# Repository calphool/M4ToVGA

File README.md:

# M4ToVGA

M4ToVGA is an FPGA hardware project that allows you to connect your TRS-80 Model 4 or TRS-80 Model 3 to a VGA monitor.  

Although everyone loves the warm glow of a 1980s CRT, these devices are slowly dying (or in my case I received a vintage TRS-80 Model 4 in the mail with a crushed CRT and needed an alternative.)

This project is built around the Cyclone IV FPGA, and more specifically the Core EP4CE6 board that is super cheap (around $20) and contains more than enough logic fabric to do the job.

## Theory of Operation

Although you can find composite boards that will convert the video signals from a TRS-80 Model 3/4 to a composite video signal that can be used with an NTSC television, most of these are based on the video output circuitry of the TRS-80 Model 1, which contains a video mixing circuit capable of mixing vsync, hsync, and video out into a *roughly* conforming NTSC composite signal.  Unfortunately, the timing of the Model 3/4 video output is a little bit different than the Model 1, and thus many people struggle to use these composite boards successfully unless their television has a means of shifting and stretching the video signal.

Although I was able to get one of these circuits to work *more or less*, I was unsatisfied with the results, and I wanted to learn how to code Verilog for FPGAs anyway, so I thought this would be a good time to learn.

The code has five main blocks (or modules).  

* It has a "top" module whose job is to stitch all the submodules together into a meaningful circuit.  
* The submodules include a PLL based clock for the VGA signal (25MHZ for 640x480 resolution).  
* The next submodule is a framebuffer that is 153,600 x 1 bits, which works to store a 640 x 240 array of pixels, the maximum resolution of a TRS-80 Model 3/4.  Those two submodules were generated in Quartus II using wizards.  
* Next is a VGA output module whose job is to take in the VGA clock and continuously scan through the framebuffer and display what it sees there.  It has a sub-sub-module whose job is to produce vga hsync and vsync as well as inform the VGA output module when the signal is "in the display zone," as opposed to one of the vertical or horizontal blank areas.
* Finally is the m4_input module, whose job is to monitor the Model 3/Model 4 hsync, vsync, dot clock, and video signals, interpret them, and turn them into bits (pixels) in the dual port frame buffer.
 The dotclk signal was actually removed in the M3 code because we don't need it. The M3 only has one resolution and we can synthesize the dotclk and keep it in aligned using 
hsync.  It is *probably* possible to remove it for the M4 as well, but I would have to contend with the fact that the dot clock changes due to the M4's ability to switch between 64 and 80 column mode.

## Details

Below you will see oscilloscope pictures showing the hsync, vsync, and video traces from a TRS-80 Model 4 (ignore the "Model 3" text, it's a typo).  

These signals are all driven and synchronized by an underlying "dot clock."

These signals are what we needed to transform into a VGA signal, and what the m4_input submodule contends with.

Below you see a graphic of the top module that ties together all the submodules.

## Status

**2021, April 18**

A few updates.  First, I bought a Nandland Go board because I like how the designer (Russell) has put together a lot of training material.  I am thinking of going through 
his training projects to pick up tips / tricks.  No intent to convert the MXToVGA projects away from Altera, but I sure would like to get a more solid understanding of 
how hardware engineers like Russell build rock solid projects.  Oh, I also updated all the code in this repo to use Russell's naming standard.  He's right, it makes the 
code easier to understand.

As you may have figured out, I have bifurcated (trifurcated?) the project into three separate repositories (M4ToVGA, M2ToVGA, and M3ToVGA).  M4ToVGA and M3ToVGA are known to be working.
M2ToVGA is *close* to working, but seems to still exhibit some jitter.  I am waiting to borrow an M2 from someone in order to work out what exactly is going on.  Since the 
fix for the M3ToVGA from the M4ToVGA base code was to add another flip flop in the video input chain, I have little doubt that there is something similar going on somewhere,
in the M2ToVGA code, but the trick is finding it, and that takes a degree of trial and error.  Once I get three separate repos that work (and thus can ship a working board for all three 
systems), I will probably spend some time figuring out how I can merge the code bases.  They're *very* similar, so it seems reasonable that they could be merged, which 
would be easier to maintain.  

I also just bought some LM1881 sync splitter chips, and so I'll be embarking on an effort to figure out if it's possible to build a 
VGA adapter for the Model 1 that does not require modifying the system.  In theory, if I can get the signals split out, then the exercise becomes similar to the MXToVGA 
projects.  It would be nice to build it so that it doesn't need an external power source, and I think there's a +5V signal available in the video DIN, but I'm not sure 
how much current can be drawn from it.  More details later.

**2021, February 20**

Updated the M4ToVGA code to get rid of the top and bottom line.  Now it has a temporary logo that disappears after 10 seconds.

**2021, January 20**

I have begun shipping the first few copies of the 1.1 VGA board, which includes some location fixes for components.  There is one remaining "slighly off"
location for the power pins for the FPGA, but it is close enough that if I solder the pins after the two boards are mated it still works okay.  I 
will fix it in the 1.2 version of the board if I get through the 20+ 1.1 boards I have.  I may also do something different with the location of the 
power regulators.  They are oriented vertically toward the bottom of the board, which is a little non-aesthetic since they stand up like tombstones.

I want to get the board out to a few people before opening the flood gates.  I'm well aware that it has only been tested on my M4, and so as people 
begin trying it on M2s and M3s, I want to see what the results are.  It *appears* that it should work just fine, and may even work on an M1 with the 
right signal placement, but I'm well aware that with hardware you never know for sure until you've actually seen the results.

I did some experimentation with providing my own on-board clock and ignoring the dot clock from the TRS-80, which produced something that *kind of* works. I 
would need to oversample the signals considerably (probably at least 10X) and then come up with an algorithm for using the oversampled 
signals, and at this point that's just a bit beyond my Verilog skills.  I'll probably keep toying around with it over time.  It's clearly possible, but 
just not as easy as taking the dot clock from the motherboard and using it to synchronize the incoming video.  I suspect this is why many -ToVGA boards 
have subtle issues that require options and menu systems to work around.  For now the production version of the board still requires the dot clock.

**2020, December 15**

I did eventually figure out how to clear the BRAM when the mode switches from 80 to 64 column mode.  It took way more work than I expected.  The solution was 
relatively simple, but getting there was not.

Got the PCB, populated it.  Worked as intended.  I'm working on another revision though because I don't care for a few of the placement decisions I made.
I also need to add a pin header so that the board can be used on something other than the Model 3/4 AMP connector.  I also realized that soldering 0603 LEDs 
is a pain in the neck, so I switched all those out to small through-hole LEDs.

I don't care for the DOT CLK situation.  I'd like to get rid of the dot clock, but I haven't come up with a solution yet.

I've also been digging into DVI/HDMI via FPGA.  There is apparently an open source HDMI implementation now, so the question is will it work for a Cyclone IV
board?  It looks like it might.  How cool would it be to have simultaneous VGA and HDMI out?  Might be a pipe dream, but it's something I'll keep digging into.
We'll see...

**2020, November 26**

Happy Thanksgiving for those in the USA!  It's not exactly a pleasant one for most folks as the "human-malware" continues to spread and 
most folks are limiting their get-togethers in one form or another.

Well, I made some tweaks to the code to deal with the fact that 80-column mode on the TRS-80 Model 4 has a different dot clock than 
64 column mode.  Without these changes the right side of 80 column mode was chopped off.  At vertical blank, the code resets the 
counter it uses to count how many dots there were per horizontal line, which allows the code to switch back and forth between modes.

There's one remaining issue, which is that since 80 column mode uses the entire screen worth of pixels, when you switch back to 
64 column mode there is sometimes garbage left on the right and left sides of the screen.  I'll have to work some kind of "one frame of 
clearing the dual port ram" when a change is detected into the design.

I also think I'd like to have some way to change the amount that the screen shifts left/right and maybe top/bottom.  Ideally it would 
be a potentiometer or rotational encoder, though I'm not sure how you interface either of them to an FPGA and I'd rather not have to 
introduce an ADC to the design if I can help it.  Ideally two additional pots/encoders would let you shrink or expand the screen as well,
but that will probably have to wait a bit.  In any event, I'll be digging into how to potentiometers/encoders these into the design shortly.

**2020, November 23**

The current version works, but isn't complete.  I'll need to design a PCB next and finish its testing to produce a version 1.0.

## License
[MIT](https://choosealicense.com/licenses/mit/)

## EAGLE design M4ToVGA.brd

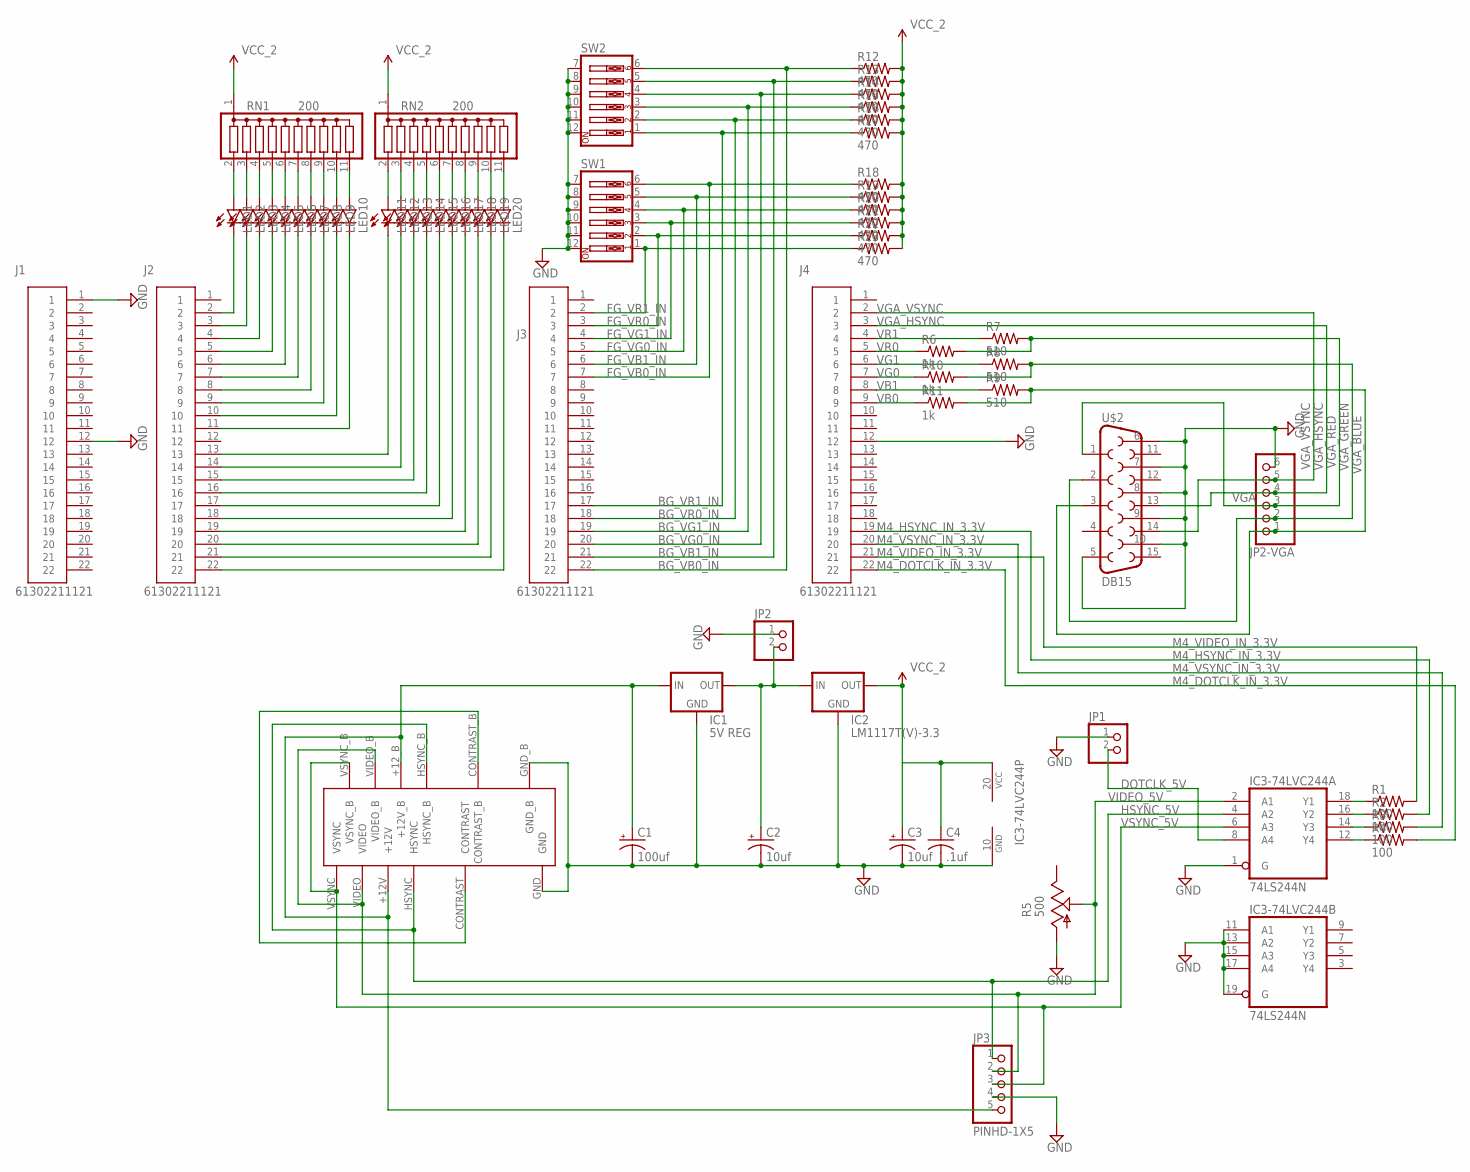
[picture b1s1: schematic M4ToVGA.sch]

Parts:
C1: 100uf; E2,5-5
C2, C3: 10uf; E2,5-5
C4: .1uf; C025-025X050
IC1: 5V REG; 78XXS
IC2: LM1117T(V)-3.3; TO220V
IC3-74LVC244: 74LS244N; DIL20
J1, J2, J3, J4: 61302211121
JP1, JP2: PINHD-1X2; 1X02
JP2-VGA: VGA; 1X06
JP3: PINHD-1X5; 1X05
LED1, LED2, LED3, LED4, LED5, LED6, LED7, LED8, LED9, LED10, LED11, LED12, LED13, LED14, LED15, LED16, LED17, LED18, LED19, LED20: LED3MM
R1, R2, R3, R4: 100; 0204/7
R5: 500; B25P
R6, R10, R11: 1k; 0204/7
R7, R8, R9: 510; 0204/7
R12, R13, R14, R15, R16, R17, R18, R19, R20, R21, R22, R23: 470; 0204/7
RN1, RN2: 200; SIL11
SW1, SW2: SW_DIP-6; EDG-06
U$1: AMP-583479-1-CARD-EDGE; AMP583479-1
U$2: DB15

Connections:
+5V: C2.+, IC1.OUT, IC2.3 (IN), JP2.2
+12V: C1.+, IC1.IN, JP3.5, U$1.+12V, U$1.+12_B (+12V_B)
BG_VB0_IN: J3.22, R12.1, SW2.6
BG_VB1_IN: J3.21, R13.1, SW2.5
BG_VG0_IN: J3.20, R14.1, SW2.4
BG_VG1_IN: J3.19, R15.1, SW2.3
BG_VR0_IN: J3.18, R16.1, SW2.2
BG_VR1_IN: J3.17, R17.1, SW2.1
DOTCLK_5V: IC3-74LVC244.8 (A4), JP1.2
FG_VB0_IN: J3.7, R18.1, SW1.6
FG_VB1_IN: J3.6, R19.1, SW1.5
FG_VG0_IN: J3.5, R20.1, SW1.4
FG_VG1_IN: J3.4, R21.1, SW1.3
FG_VR0_IN: J3.3, R22.1, SW1.2
FG_VR1_IN: J3.2, R23.1, SW1.1
GND: C1.-, C2.-, C3.-, C4.2, IC1.GND, IC2.1 (GND), IC3-74LVC244.1 (G), IC3-74LVC244.10 (GND), IC3-74LVC244.11 (A1), IC3-74LVC244.13 (A2), IC3-74LVC244.15 (A3), IC3-74LVC244.17 (A4), IC3-74LVC244.19 (G), J1.1, J1.12, J4.12, JP1.1, JP2.1, JP2-VGA.6, JP3.4, R5.A, SW1.7, SW1.8, SW1.9, SW1.10, SW1.11, SW1.12, SW2.7, SW2.8, SW2.9, SW2.10, SW2.11, SW2.12, U$1.GND, U$1.GND_B, U$2.5, U$2.6, U$2.7, U$2.8, U$2.9, U$2.10
HSYNC_5V: IC3-74LVC244.4 (A2), JP3.1, U$1.HSYNC, U$1.HSYNC_B
M4_DOTCLK_IN_3.3V: J4.22, R4.2
M4_HSYNC_IN_3.3V: J4.19, R2.2
M4_VIDEO_IN_3.3V: J4.21, R1.2
M4_VSYNC_IN_3.3V: J4.20, R3.2
unnamed: IC3-74LVC244.18 (Y1), R1.1
unnamed: IC3-74LVC244.16 (Y2), R2.1
unnamed: IC3-74LVC244.14 (Y3), R3.1
unnamed: IC3-74LVC244.12 (Y4), R4.1
unnamed: LED1.A, RN1.2
unnamed: U$1.CONTRAST, U$1.CONTRAST_B
unnamed: LED2.A, RN1.3
unnamed: LED3.A, RN1.4
unnamed: LED4.A, RN1.5
unnamed: LED5.A, RN1.6
unnamed: LED6.A, RN1.7
unnamed: LED7.A, RN1.8
unnamed: LED8.A, RN1.9
unnamed: LED9.A, RN1.10
unnamed: LED10.A, RN1.11
unnamed: LED11.A, RN2.2
unnamed: LED12.A, RN2.3
unnamed: LED13.A, RN2.4
unnamed: LED14.A, RN2.5
unnamed: LED15.A, RN2.6
unnamed: LED16.A, RN2.7
unnamed: LED17.A, RN2.8
unnamed: LED18.A, RN2.9
unnamed: LED19.A, RN2.10
unnamed: LED20.A, RN2.11
OUTPUTLEDA_0: J2.11, LED10.K (C)
OUTPUTLEDA_1: J2.10, LED9.K (C)
OUTPUTLEDA_2: J2.9, LED8.K (C)
OUTPUTLEDA_3: J2.8, LED7.K (C)
OUTPUTLEDA_4: J2.7, LED6.K (C)
OUTPUTLEDA_5: J2.6, LED5.K (C)
OUTPUTLEDA_6: J2.5, LED4.K (C)
OUTPUTLEDA_7: J2.4, LED3.K (C)
OUTPUTLEDA_8: J2.3, LED2.K (C)
OUTPUTLEDA_9: J2.2, LED1.K (C)
OUTPUTLEDB_0: J2.22, LED20.K (C)
OUTPUTLEDB_1: J2.21, LED19.K (C)
OUTPUTLEDB_2: J2.20, LED18.K (C)
OUTPUTLEDB_3: J2.19, LED17.K (C)
OUTPUTLEDB_4: J2.18, LED16.K (C)
OUTPUTLEDB_5: J2.17, LED15.K (C)
OUTPUTLEDB_6: J2.16, LED14.K (C)
OUTPUTLEDB_7: J2.15, LED13.K (C)
OUTPUTLEDB_8: J2.14, LED12.K (C)
OUTPUTLEDB_9: J2.13, LED11.K (C)
VB0: J4.9, R11.1
VB1: J4.8, R9.1
VCC_2: C3.+, C4.1, IC2.2 (OUT), IC3-74LVC244.20 (VCC), R12.2, R13.2, R14.2, R15.2, R16.2, R17.2, R18.2, R19.2, R20.2, R21.2, R22.2, R23.2, RN1.1, RN2.1
VG0: J4.7, R10.1
VG1: J4.6, R8.1
VGA_BLUE: JP2-VGA.1, R9.2, R11.2, U$2.3
VGA_GREEN: JP2-VGA.2, R8.2, R10.2, U$2.2
VGA_HSYNC: J4.3, JP2-VGA.4, U$2.13
VGA_RED: JP2-VGA.3, R6.2, R7.2, U$2.1
VGA_VSYNC: J4.2, JP2-VGA.5, U$2.14
VIDEO_5V: IC3-74LVC244.2 (A1), JP3.2, R5.S, U$1.VIDEO, U$1.VIDEO_B
VR0: J4.5, R6.1
VR1: J4.4, R7.1
VSYNC_5V: IC3-74LVC244.6 (A3), JP3.3, U$1.VSYNC, U$1.VSYNC_B

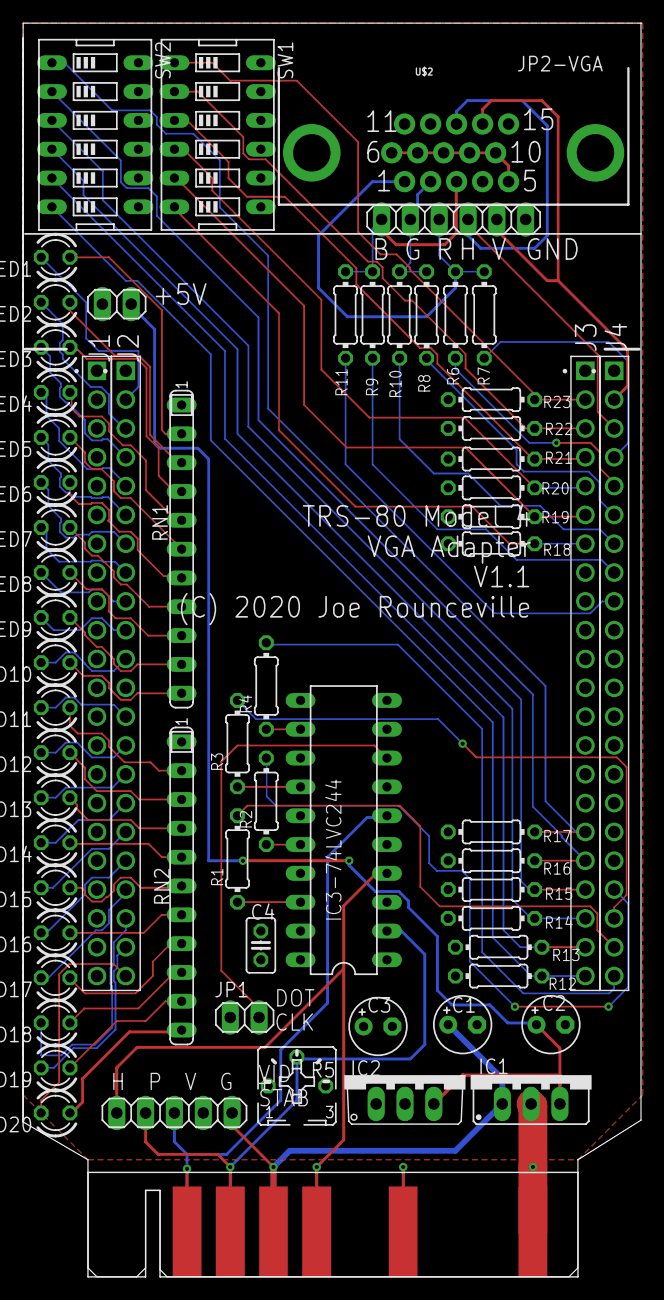
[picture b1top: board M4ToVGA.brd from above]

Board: 2 copper layers, 54.5 x 110.5 mm, 64 parts (0 on the bottom side), 80 nets.

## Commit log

2020-11-23 initial upload
2020-11-27 added gitignore
2020-11-27 recent changes related to left/right shifting
2020-11-27 clean up Quartus II files accidentally put in repo
2020-12-01 fixed mem clear behavior when switching 80 colum and 64 column modes
2020-12-01 comments for m4_input
2020-12-14 added code for foreground/background color change
2020-12-16 added Eaglecad drawings for board
2020-12-16 readme update
2020-12-16 fixed readme
2021-01-24 updating stuff Quartus did
2021-01-26 put code back in place to show resolution counter
2021-01-26 changed dip switches so that one switch does both background and foreground color, freeing up other dip switch
2021-01-27 added code to allow left / right shift in 800 pixel mode via dip switch
2021-01-27 adding binary for usb blaster
2021-01-27 comment clean up
2021-01-27 readme fix
2021-01-27 added pdf of schematic
2021-02-02 added current installation instructions PDF
2021-02-02 added picture to installation documentation for transmission line 'hack' if necessary
2021-02-02 minor update to docs
2021-02-02 changed usb blaster binary to match current source code
2021-02-04 sync upload
2021-02-20 update to get rid of top and bottom line
2021-04-11 updated LED behavior
2021-04-12 synced M4 code to M3 code for input block
2021-04-18 updated variable names
2021-04-18 spelling mistake

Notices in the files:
M4ToVGA.brd:
(C) 2020 Joe Rounceville
parts and their libraries:
SparkFun-Retired: Licensing: Creative Commons ShareAlike 4.0 International - https://creativecommons.org/licenses/by-sa/4.0
